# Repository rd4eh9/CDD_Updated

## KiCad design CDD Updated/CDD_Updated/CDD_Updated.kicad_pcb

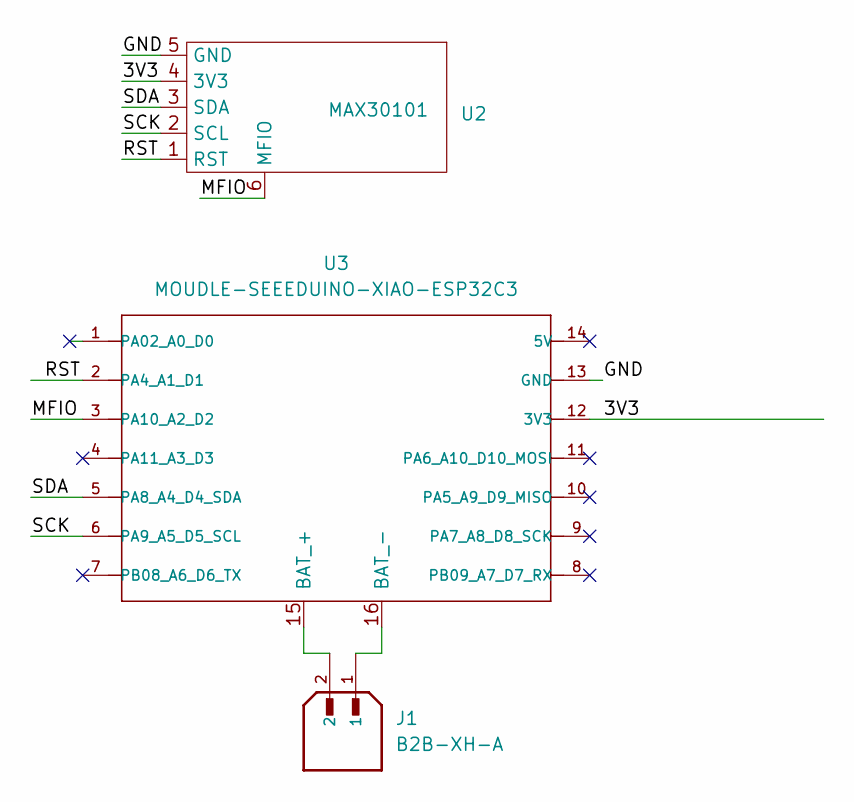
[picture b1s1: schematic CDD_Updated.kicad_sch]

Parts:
J1: B2B-XH-A; JST_B2B-XH-A; PARTREV N/A
U2: MAX30101; MAX30101_PPG_Sensor
U3: MOUDLE-SEEEDUINO-XIAO-ESP32C3; MOUDLE14P-SMD-2.54-21X17.8MM

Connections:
/3V3: U2.4 (3V3), U3.12 (3V3)
/GND: U2.5 (GND), U3.13 (GND)
/MFIO: U2.6 (MFIO), U3.3 (PA10_A2_D2)
/RST: U2.1 (RST), U3.2 (PA4_A1_D1)
/SCK: U2.2 (SCL), U3.6 (PA9_A5_D5_SCL)
/SDA: U2.3 (SDA), U3.5 (PA8_A4_D4_SDA)
unnamed: J1.2, U3.15 (BAT_+)
unnamed: J1.1, U3.16 (BAT_-)

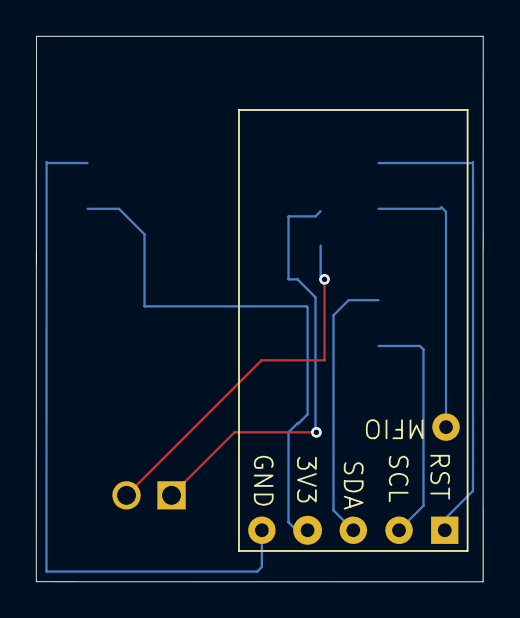
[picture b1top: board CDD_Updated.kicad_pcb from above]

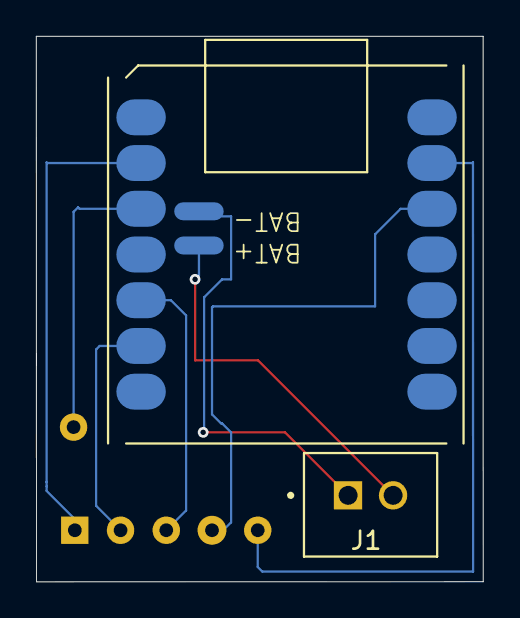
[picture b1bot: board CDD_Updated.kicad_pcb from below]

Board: 4 copper layers, 24.8 x 30.3 mm, 3 parts (2 on the bottom side), 8 nets.

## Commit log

2025-03-06 update files
2025-03-07 Updated footprints and PCB
2025-03-11 Added temperature reading to ppg_test_sketch; not tested yet
2025-03-15 Update KiCAD files and route PCB
2025-03-17 Update PCB
2026-01-26 Added file for recording data to google sheet
2026-02-16 test commit
2026-02-16 pushing so on the same page
2026-02-16 created new files
2026-02-16 push
2026-02-23 Added reading for IR and Red data
2026-02-24 Added raw reading of ir and red but is only outputting 0
2026-03-09 Tried to connect to wifi and also change LED readings
2026-03-24 updates w code sayeed sent in gc
2026-03-24 no tab issue
2026-03-25 New script
    Python script 1st iteration to try and store data in csv without wifi
2026-03-30 fixed scripting
2026-04-02 sample rate & pwm testing_python_csv.ino
    Added code to specify sampling rate and pwm so it won't go to default settings (Ben)
2026-04-06 update pcb and schematic - remove extra sensors
2026-04-11 Updated python and arduino code to record raw IR and Red data, started data collection
2026-04-17 Updated polling speed
2026-04-19 optimized pcb for size
2026-04-19 fixed routing error
